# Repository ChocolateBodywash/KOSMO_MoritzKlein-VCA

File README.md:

## KOSMO Format Moritz Klein VCA

A KOSMO format of Moritz Klein’s VCA

This was my first dip into PCB design and oh boy, it would have made more sense to start with the simpler ADSR. There were a lot of things I could have done more efficiently and possibly better (adding normalization between VCAs) but it works.

---
Note: This was created by a hobbyist with no formal engineering training outside various late night YouTube binges. 
I’ve confirmed these designs to work but I make no guarantees on the design working efficiently.. or working at all.

Additional credit: Analog Output (Richard Holmes) for footprint libraries and front panel templates.

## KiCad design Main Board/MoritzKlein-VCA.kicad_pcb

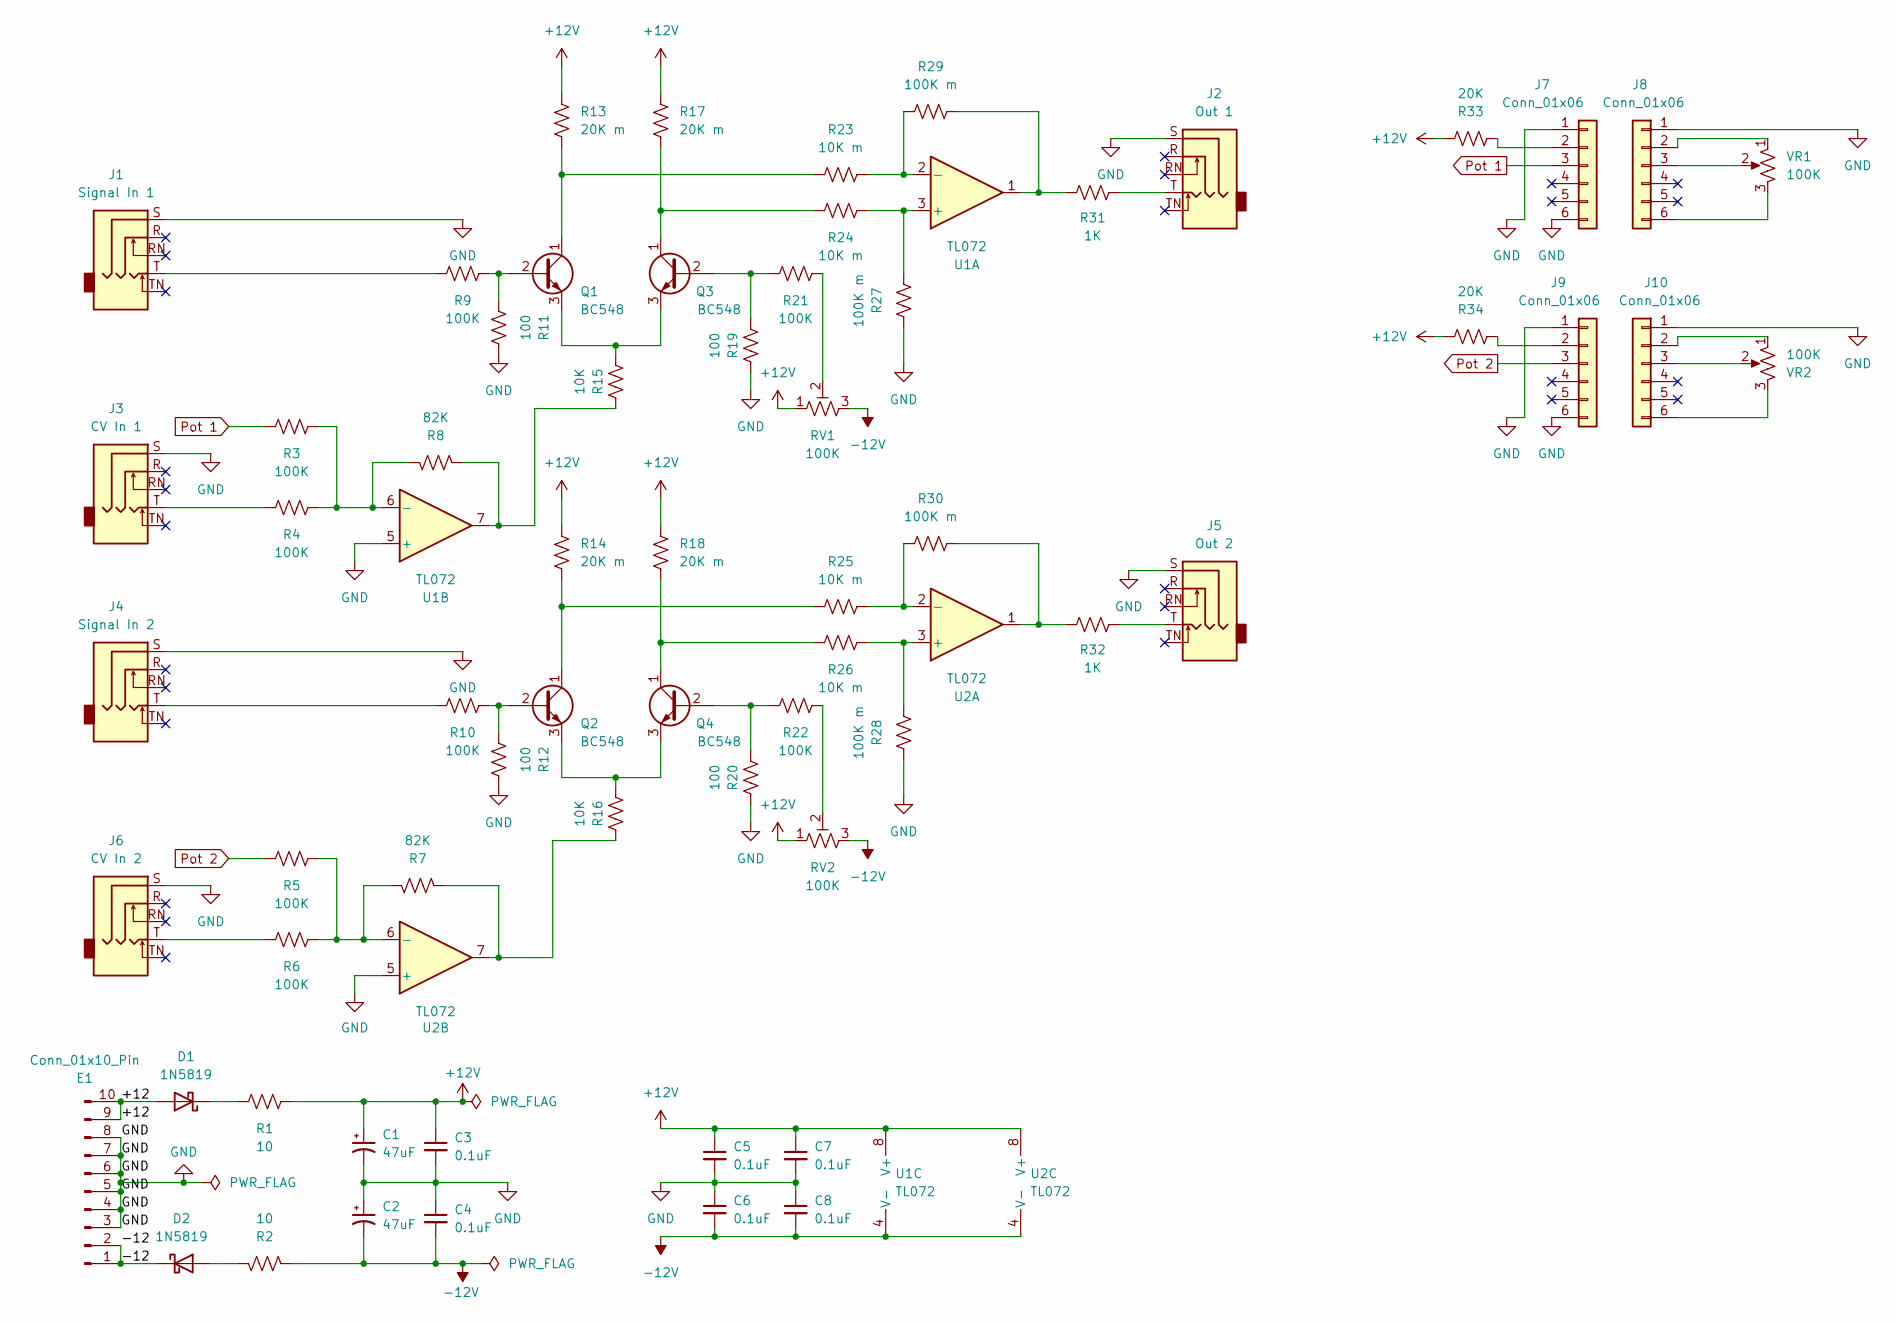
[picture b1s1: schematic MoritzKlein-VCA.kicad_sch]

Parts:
C1, C2: 47uF; CP_Radial_D5.0mm_P2.50mm
C3, C4, C5, C6, C7, C8: 0.1uF; C_Disc_D3.0mm_W1.6mm_P2.50mm
D1, D2: 1N5819; D_DO-41_SOD81_P10.16mm_Horizontal
E1: Conn_01x10_Pin; Pins_2x05_2.54mm_TH_EurorackPower_Shrouded
J1: Signal In 1; Jack_6.35mm_PJ_629HAN
J2: Out 1; Jack_6.35mm_PJ_629HAN
J3: CV In 1; Jack_6.35mm_PJ_629HAN
J4: Signal In 2; Jack_6.35mm_PJ_629HAN
J5: Out 2; Jack_6.35mm_PJ_629HAN
J6: CV In 2; Jack_6.35mm_PJ_629HAN
J7, J8, J9, J10: Conn_01x06; PinHeader_1x06_P2.54mm_Vertical
Q1, Q2, Q3, Q4: BC548; TO-92_Inline
R1, R2: 10; R_Axial_DIN0207_L6.3mm_D2.5mm_P10.16mm_Horizontal
R3, R4, R5, R6, R9, R10, R21, R22: 100K; R_Axial_DIN0207_L6.3mm_D2.5mm_P10.16mm_Horizontal
R7, R8: 82K; R_Axial_DIN0207_L6.3mm_D2.5mm_P10.16mm_Horizontal
R11, R12, R19, R20: 100; R_Axial_DIN0207_L6.3mm_D2.5mm_P10.16mm_Horizontal
R13, R14, R17, R18: 20K m; R_Axial_DIN0207_L6.3mm_D2.5mm_P10.16mm_Horizontal
R15, R16: 10K; R_Axial_DIN0207_L6.3mm_D2.5mm_P10.16mm_Horizontal
R23, R24, R25, R26: 10K m; R_Axial_DIN0207_L6.3mm_D2.5mm_P10.16mm_Horizontal
R27, R28, R29, R30: 100K m; R_Axial_DIN0207_L6.3mm_D2.5mm_P10.16mm_Horizontal
R31, R32: 1K; R_Axial_DIN0207_L6.3mm_D2.5mm_P10.16mm_Horizontal
R33, R34: 20K; R_Axial_DIN0207_L6.3mm_D2.5mm_P10.16mm_Horizontal
RV1, RV2: 100K; Potentiometer_Bourns_3296W_Vertical
U1, U2: TL072; DIP-8pin_TH
VR1, VR2: 100K; Potentiometer_Alpha_RD901F-40-00D_Single_Vertical

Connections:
+12V: C1.1, C3.1, C5.1, C7.1, R1.2, R13.1, R14.1, R17.1, R18.1, R33.2, R34.2, RV1.1, RV2.1, U1.8 (V+), U2.8 (V+)
-12V: C2.2, C4.2, C6.2, C8.2, R2.2, RV1.3, RV2.3, U1.4 (V-), U2.4 (V-)
/+12: D1.2 (A), E1.9, E1.10
/-12: D2.1 (K), E1.1, E1.2
GND: C1.2, C2.1, C3.2, C4.1, C5.2, C6.1, C7.2, C8.1, E1.3, E1.4, E1.5, E1.6, E1.7, E1.8, J1.S, J2.S, J3.S, J4.S, J5.S, J6.S, J7.1, J7.6, J8.1, J9.1, J9.6, J10.1, R11.2, R12.2, R19.2, R20.2, R27.2, R28.2, U1.5 (+), U2.5 (+)
unnamed: D1.1 (K), R1.1
unnamed: D2.2 (A), R2.1
unnamed: J1.T, R9.1
unnamed: J2.T, R31.2
unnamed: J3.T, R4.1
unnamed: J4.T, R10.1
unnamed: J5.T, R32.2
unnamed: J6.T, R6.1
unnamed: J7.2, R33.1
unnamed: J8.2, VR1.1
unnamed: J8.3, VR1.2
unnamed: J8.6, VR1.3
unnamed: J9.2, R34.1
unnamed: J10.2, VR2.1
unnamed: J10.3, VR2.2
unnamed: J10.6, VR2.3
unnamed: Q1.2 (B), R9.2, R11.1
unnamed: Q1.1 (C), R13.2, R23.1
unnamed: Q1.3 (E), Q3.3 (E), R15.1
unnamed: Q2.2 (B), R10.2, R12.1
unnamed: Q2.1 (C), R14.2, R25.1
unnamed: Q2.3 (E), Q4.3 (E), R16.1
unnamed: Q3.2 (B), R19.1, R21.1
unnamed: Q3.1 (C), R17.2, R24.1
unnamed: Q4.2 (B), R20.1, R22.1
unnamed: Q4.1 (C), R18.2, R26.1
unnamed: R8.2, R15.2, U1.7
unnamed: R7.2, R16.2, U2.7
unnamed: R21.2, RV1.2
unnamed: R22.2, RV2.2
unnamed: R29.2, R31.1, U1.1
unnamed: R30.2, R32.1, U2.1
unnamed: R24.2, R27.1, U1.3 (+)
unnamed: R23.2, R29.1, U1.2 (-)
unnamed: R3.2, R4.2, R8.1, U1.6 (-)
unnamed: R26.2, R28.1, U2.3 (+)
unnamed: R25.2, R30.1, U2.2 (-)
unnamed: R5.2, R6.2, R7.1, U2.6 (-)
Pot 1: J7.3, R3.1
Pot 2: J9.3, R5.1

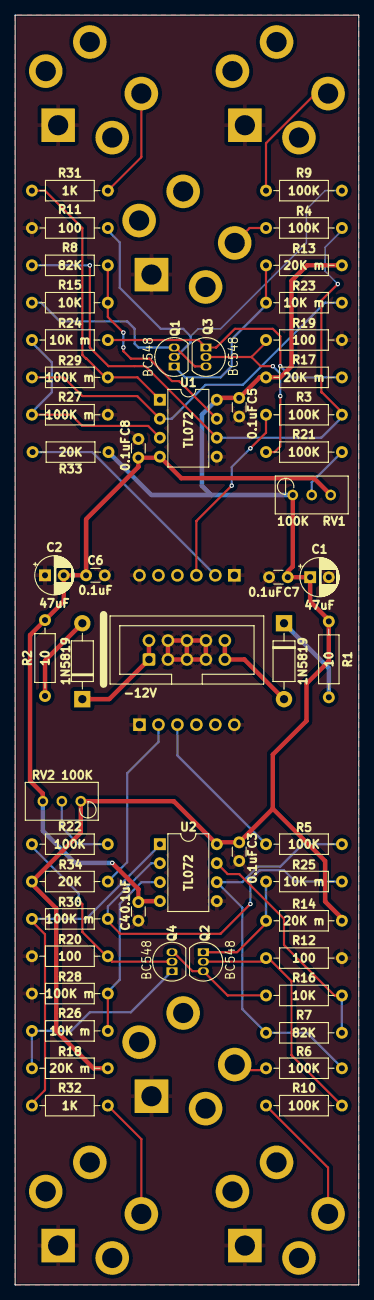
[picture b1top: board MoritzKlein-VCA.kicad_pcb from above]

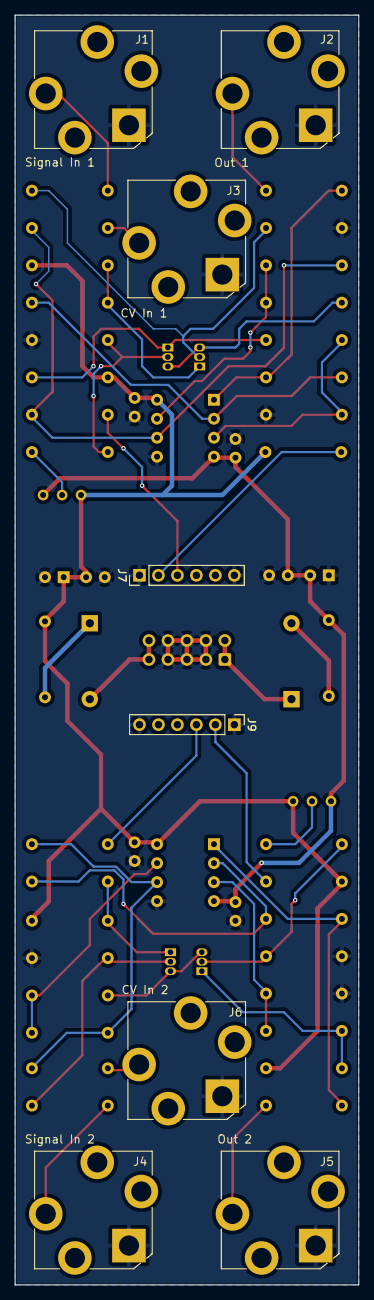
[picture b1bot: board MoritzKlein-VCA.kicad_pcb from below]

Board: 2 copper layers, 46.0 x 170.0 mm, 61 parts (8 on the bottom side), 39 nets.

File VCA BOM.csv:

Reference,Value,Datasheet,Package,Qty
"C1,C2",47uF,~,Electrolytic Capacitor,2
"C3,C4,C5,C6,C7,C8",0.1uF,~,Ceramic Disc Capacitor,6
"D1,D2",1N5819,http://www.vishay.com/docs/88525/1n5817.pdf,Diode_THT:D_DO-41_SOD81_P10.16mm_Horizontal,2
E1,Conn_02x05_Pin,~,Pins_2x05_2.54mm_TH_EurorackPower_Shrouded,1
J1,Signal In 1,~,Jack_6.35mm,1
J2,Out 1,~,Jack_6.35mm,1
J3,CV In 1,~,Jack_6.35mm,1
J4,Signal In 2,~,Jack_6.35mm,1
J5,Out 2,~,Jack_6.35mm,1
J6,CV In 2,~,Jack_6.35mm,1
"J7,J8,J9,J10",Conn_01x06,~,Connector_PinHeader_2.54mm:PinHeader_1x06_P2.54mm_Vertical,4
"Q1,Q2,Q3,Q4",BC548,https://www.onsemi.com/pub/Collateral/BC550-D.pdf,Package_TO_SOT_THT:TO-92_Inline,4
"VR1,VR2",B100K,,Potentiometer_Alpha_RD901F-40-00D_Single_Vertical,
"R1,R2",10,~,Metal Film 1/4 Resistor,2
"R3,R4,R5,R6,R9,R10,R21,R22,RV1,RV2",100K,~,Metal Film 1/4 Resistor,12
"R7,R8",82K,~,Metal Film 1/4 Resistor,2
"R11,R12,R19,R20",100,~,Metal Film 1/4 Resistor,4
"R13,R14,R17,R18",20K m,~,Metal Film 1/4 Resistor,4
"R15,R16",10K,~,Metal Film 1/4 Resistor,2
"R23,R24,R25,R26",10K m,~,Metal Film 1/4 Resistor,4
"R27,R28,R29,R30",100K m,~,Metal Film 1/4 Resistor,4
"R31,R32",1K,~,Metal Film 1/4 Resistor,2
"R33,R34",20K,~,Metal Film 1/4 Resistor,2
"U1,U2",TL072,http://www.ti.com/lit/ds/symlink/tl071.pdf,DIP-8_W7.62mm,2

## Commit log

2025-10-24 Upload Files
2025-10-27 Update image
2025-10-29 Upload Schematics
